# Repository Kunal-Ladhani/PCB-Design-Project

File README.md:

# PCB-Design-Project

In this project we designed a PCB cicuit for a Heat Sensing Device, made the PCB end-to-end using an Op-Amp (IC 741). I used EAGLE software to prepare the schematic of the PCB, printed that on a board, performed etching of the board, drilled the holes, and soldered all the circuit components onto it. 

+

+ 

+ This project was done for the completion of the course Electronic Instruments and Instrumentation Technology at BITS Pilani.

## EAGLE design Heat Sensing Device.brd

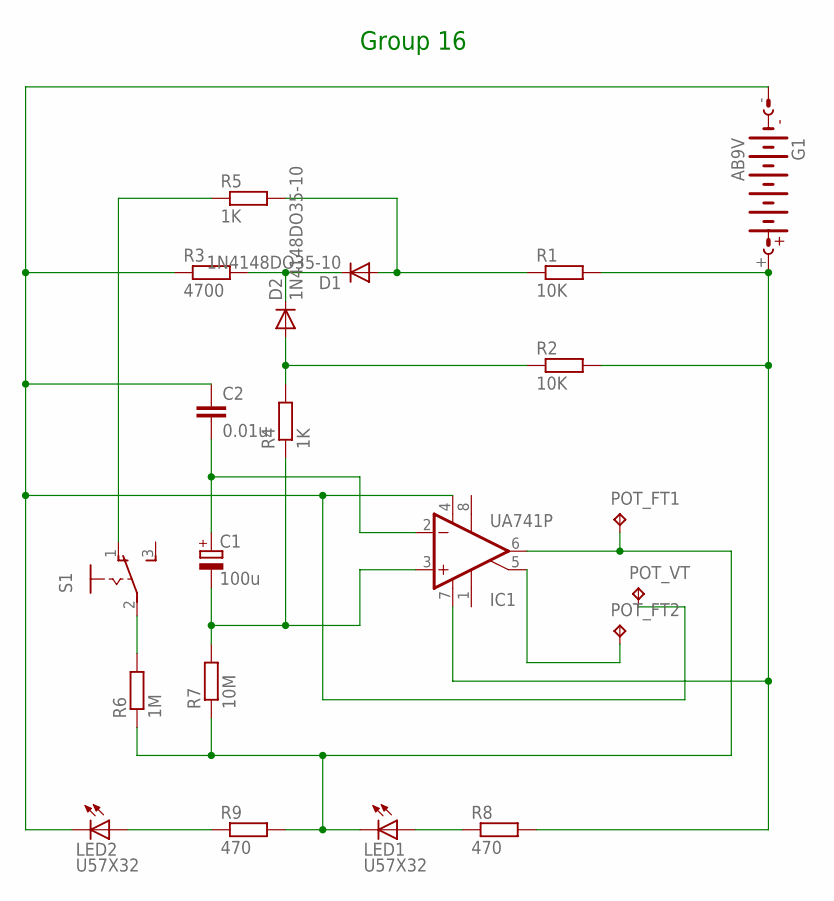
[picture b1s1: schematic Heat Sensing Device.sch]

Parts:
C1: 100u; E5-10,5
C2: 0.01u; C025-050X050
D1, D2: 1N4148DO35-10; DO35-10
G1: AB9V
IC1: UA741P; DIL08
LED1, LED2: U57X32
POT_FT1, POT_FT2: TPPAD1-17; P1-17
POT_VT: TPPAD1-17; P1-17
R1, R2: 10K; 0204/5
R3: 4700; 0204/5
R4, R5: 1K; 0204/5
R6: 1M; 0204/5
R7: 10M; 0204/5
R8, R9: 470; 0204/5
S1: 255SB

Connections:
unnamed: D1.A, R1.1, R5.2
unnamed: D1.C, D2.C, R3.2
unnamed: C1.-, IC1.3 (+IN), R4.1, R7.2
unnamed: LED2.A, R9.1
unnamed: R5.1, S1.1 (O)
unnamed: LED1.A, R8.1
unnamed: C1.+, C2.2, IC1.2 (-IN)
unnamed: IC1.5 (ON2), POT_FT2.TP
unnamed: IC1.6 (OUT), LED1.K (C), POT_FT1.TP, R6.1, R7.1, R9.2
unnamed: D2.A, R2.1, R4.2
unnamed: C2.1, G1.-, IC1.4 (V-), LED2.K (C), POT_VT.TP, R3.1
unnamed: R6.2, S1.2
unnamed: G1.+, IC1.7 (V+), R1.2, R2.2, R8.2

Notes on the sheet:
Group 16

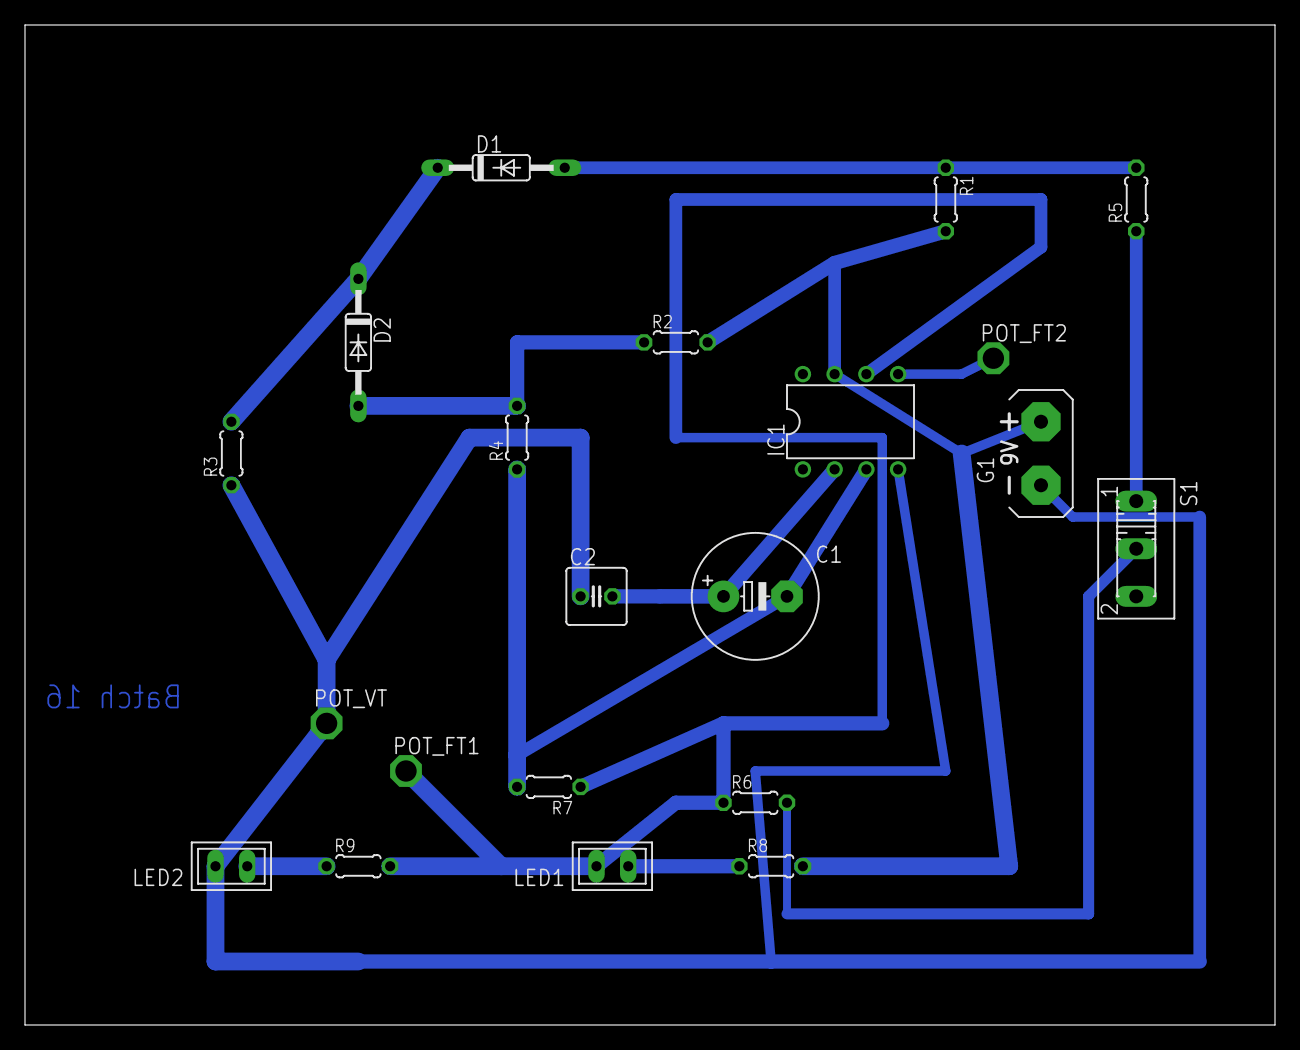
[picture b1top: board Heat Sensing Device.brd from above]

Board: 2 copper layers, 100.0 x 80.0 mm, 21 parts (0 on the bottom side), 13 nets.

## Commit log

2020-07-23 Add files via upload
    Added schematic, board and the final pdf file of the PCB.
